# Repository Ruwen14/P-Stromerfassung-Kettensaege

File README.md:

# P-Stromerfassung-Kettensaege
Projektarbeit: Schaltungstechnik Master Mechatronik
- Aufgabenstellung:
  Messung des Dreiphasenstrom eines BLDC-Motors in einer Kettensäge

- Genutzte Technologien:
  -   LTSpice (Simulation)
  -   Eagle (Platinendesign & Layout)
  -   Reflow Ofen & Löteisen (Bestückung)

# Schematic

# PCB

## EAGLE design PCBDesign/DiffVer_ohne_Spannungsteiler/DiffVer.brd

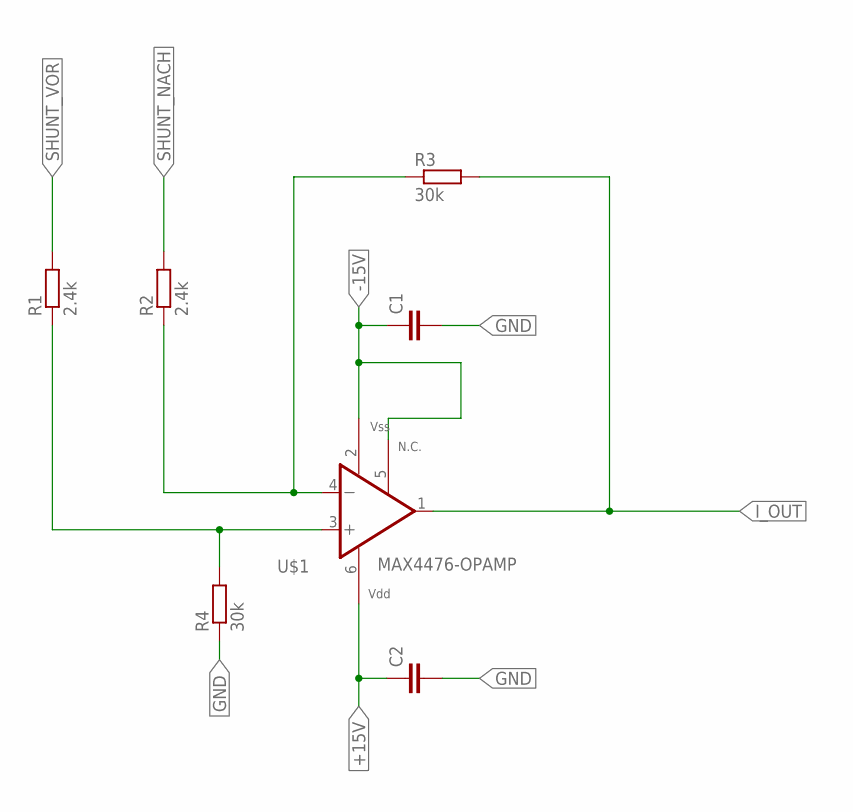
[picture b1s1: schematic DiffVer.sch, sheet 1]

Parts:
C1, C2: C-EUC0805; C0805
R1, R2: 2.4k; R0805
R3, R4: 30k; R0805
U$1: MAX4476-OPAMP; SOT23-6

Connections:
+15V: C2.1, U$1.6 (VDD); also elsewhere on the board
-15V: C1.1, U$1.2 (VSS), U$1.5 (NC); also elsewhere on the board
GND: C1.2, C2.2, R4.1; also elsewhere on the board
I_OUT: R3.2, U$1.1 (OUT); also elsewhere on the board
MINUS_OP: R2.1, R3.1, U$1.4 (-IN)
PLUS_OP: R1.1, R4.2, U$1.3 (+IN)
SHUNT_NACH: R2.2; also elsewhere on the board
SHUNT_VOR: R1.2; also elsewhere on the board

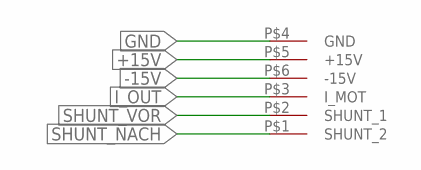
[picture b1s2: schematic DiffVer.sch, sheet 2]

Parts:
U$2: ADAPTERPLATINE_OPSHUNT

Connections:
+15V: U$2.P$5 (+15V); also elsewhere on the board
-15V: U$2.P$6 (-15V); also elsewhere on the board
GND: U$2.P$4 (GND); also elsewhere on the board
I_OUT: U$2.P$3 (I_MOT); also elsewhere on the board
SHUNT_NACH: U$2.P$1 (SHUNT_2); also elsewhere on the board
SHUNT_VOR: U$2.P$2 (SHUNT_1); also elsewhere on the board

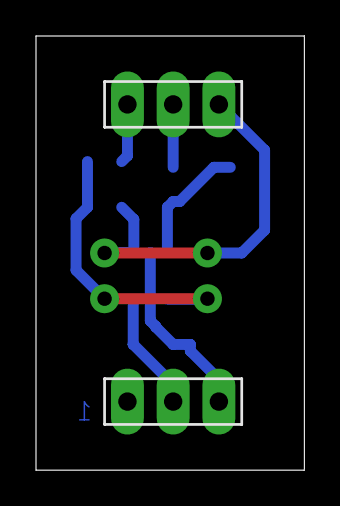
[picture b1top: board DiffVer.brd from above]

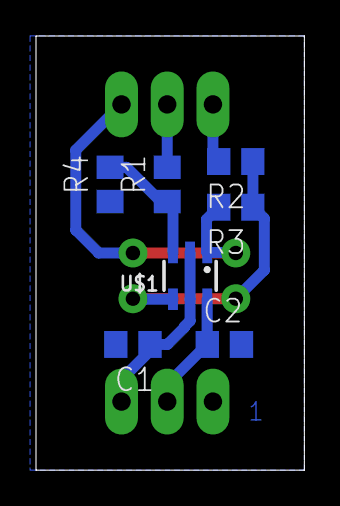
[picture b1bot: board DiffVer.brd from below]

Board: 2 copper layers, 14.9 x 24.1 mm, 8 parts (7 on the bottom side), 8 nets.

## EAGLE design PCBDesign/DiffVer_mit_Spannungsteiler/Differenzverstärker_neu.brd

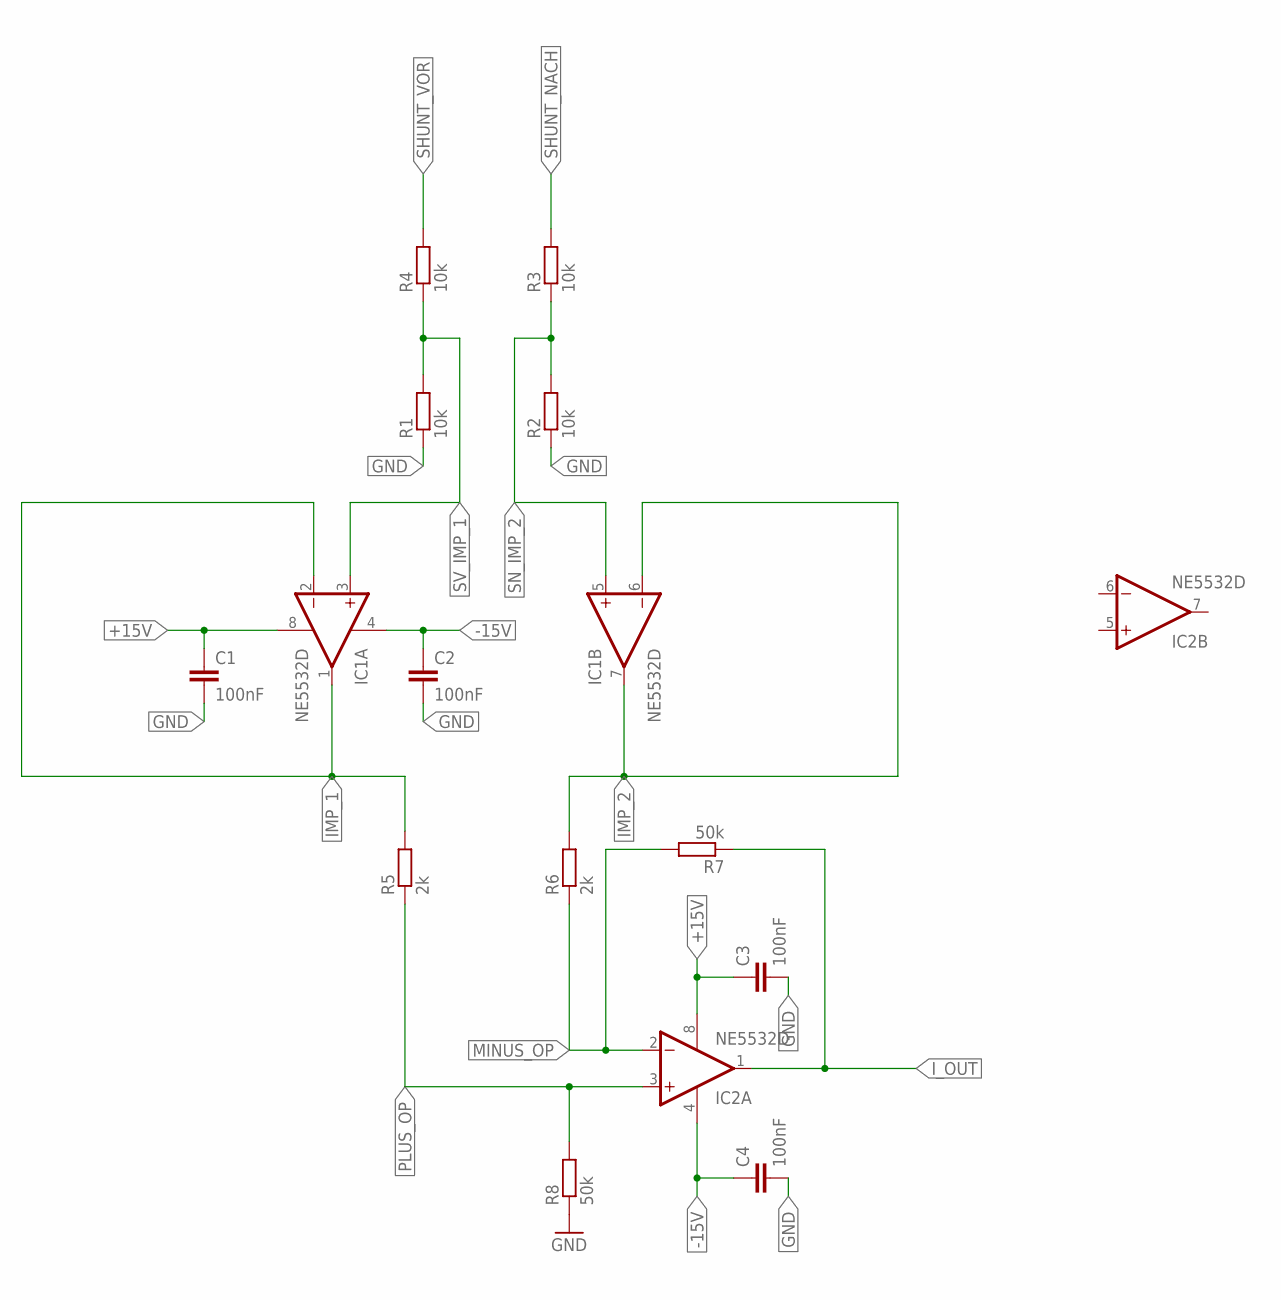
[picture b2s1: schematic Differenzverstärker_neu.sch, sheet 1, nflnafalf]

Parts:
C1, C2, C3, C4: 100nF; C0805
IC1, IC2: NE5532D; SO08
R1, R2, R3, R4: 10k; R0805
R5, R6: 2k; R0805
R7, R8: 50k; R0805

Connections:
+15V: C1.1, C3.1, IC1.8 (V+), IC2.8 (V+); also elsewhere on the board
-15V: C2.1, C4.1, IC1.4 (V-), IC2.4 (V-); also elsewhere on the board
GND: C1.2, C2.2, C3.2, C4.2, R1.1, R2.1, R8.1; also elsewhere on the board
IMP_1: IC1.1 (OUT), IC1.2 (-IN), R5.2
IMP_2: IC1.6 (-IN), IC1.7 (OUT), R6.2
I_OUT: IC2.1 (OUT), R7.1; also elsewhere on the board
MINUS_OP: IC2.2 (-IN), R6.1, R7.2
PLUS_OP: IC2.3 (+IN), R5.1, R8.2
SHUNT_NACH: R3.2; also elsewhere on the board
SHUNT_VOR: R4.2; also elsewhere on the board
SN_IMP_2: IC1.5 (+IN), R2.2, R3.1
SV_IMP_1: IC1.3 (+IN), R1.2, R4.1

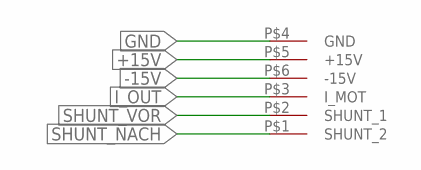
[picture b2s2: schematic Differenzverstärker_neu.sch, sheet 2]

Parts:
U$2: ADAPTERPLATINE_OPSHUNT

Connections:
+15V: U$2.P$5 (+15V); also elsewhere on the board
-15V: U$2.P$6 (-15V); also elsewhere on the board
GND: U$2.P$4 (GND); also elsewhere on the board
I_OUT: U$2.P$3 (I_MOT); also elsewhere on the board
SHUNT_NACH: U$2.P$1 (SHUNT_2); also elsewhere on the board
SHUNT_VOR: U$2.P$2 (SHUNT_1); also elsewhere on the board

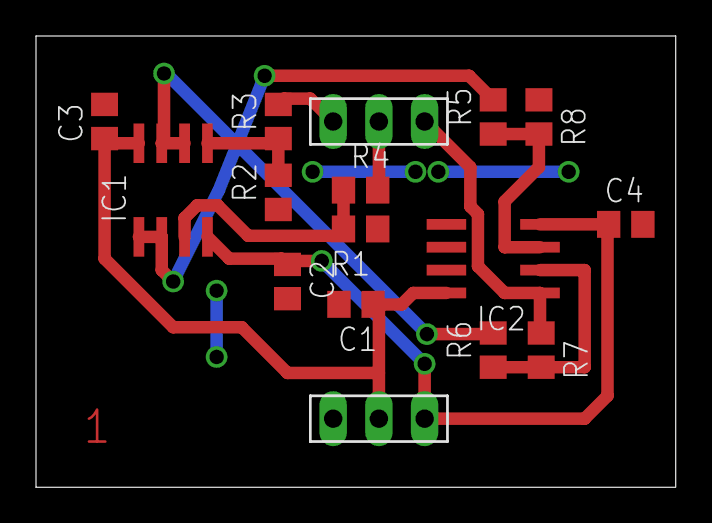
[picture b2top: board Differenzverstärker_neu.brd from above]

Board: 2 copper layers, 35.5 x 25.1 mm, 15 parts (0 on the bottom side), 12 nets.

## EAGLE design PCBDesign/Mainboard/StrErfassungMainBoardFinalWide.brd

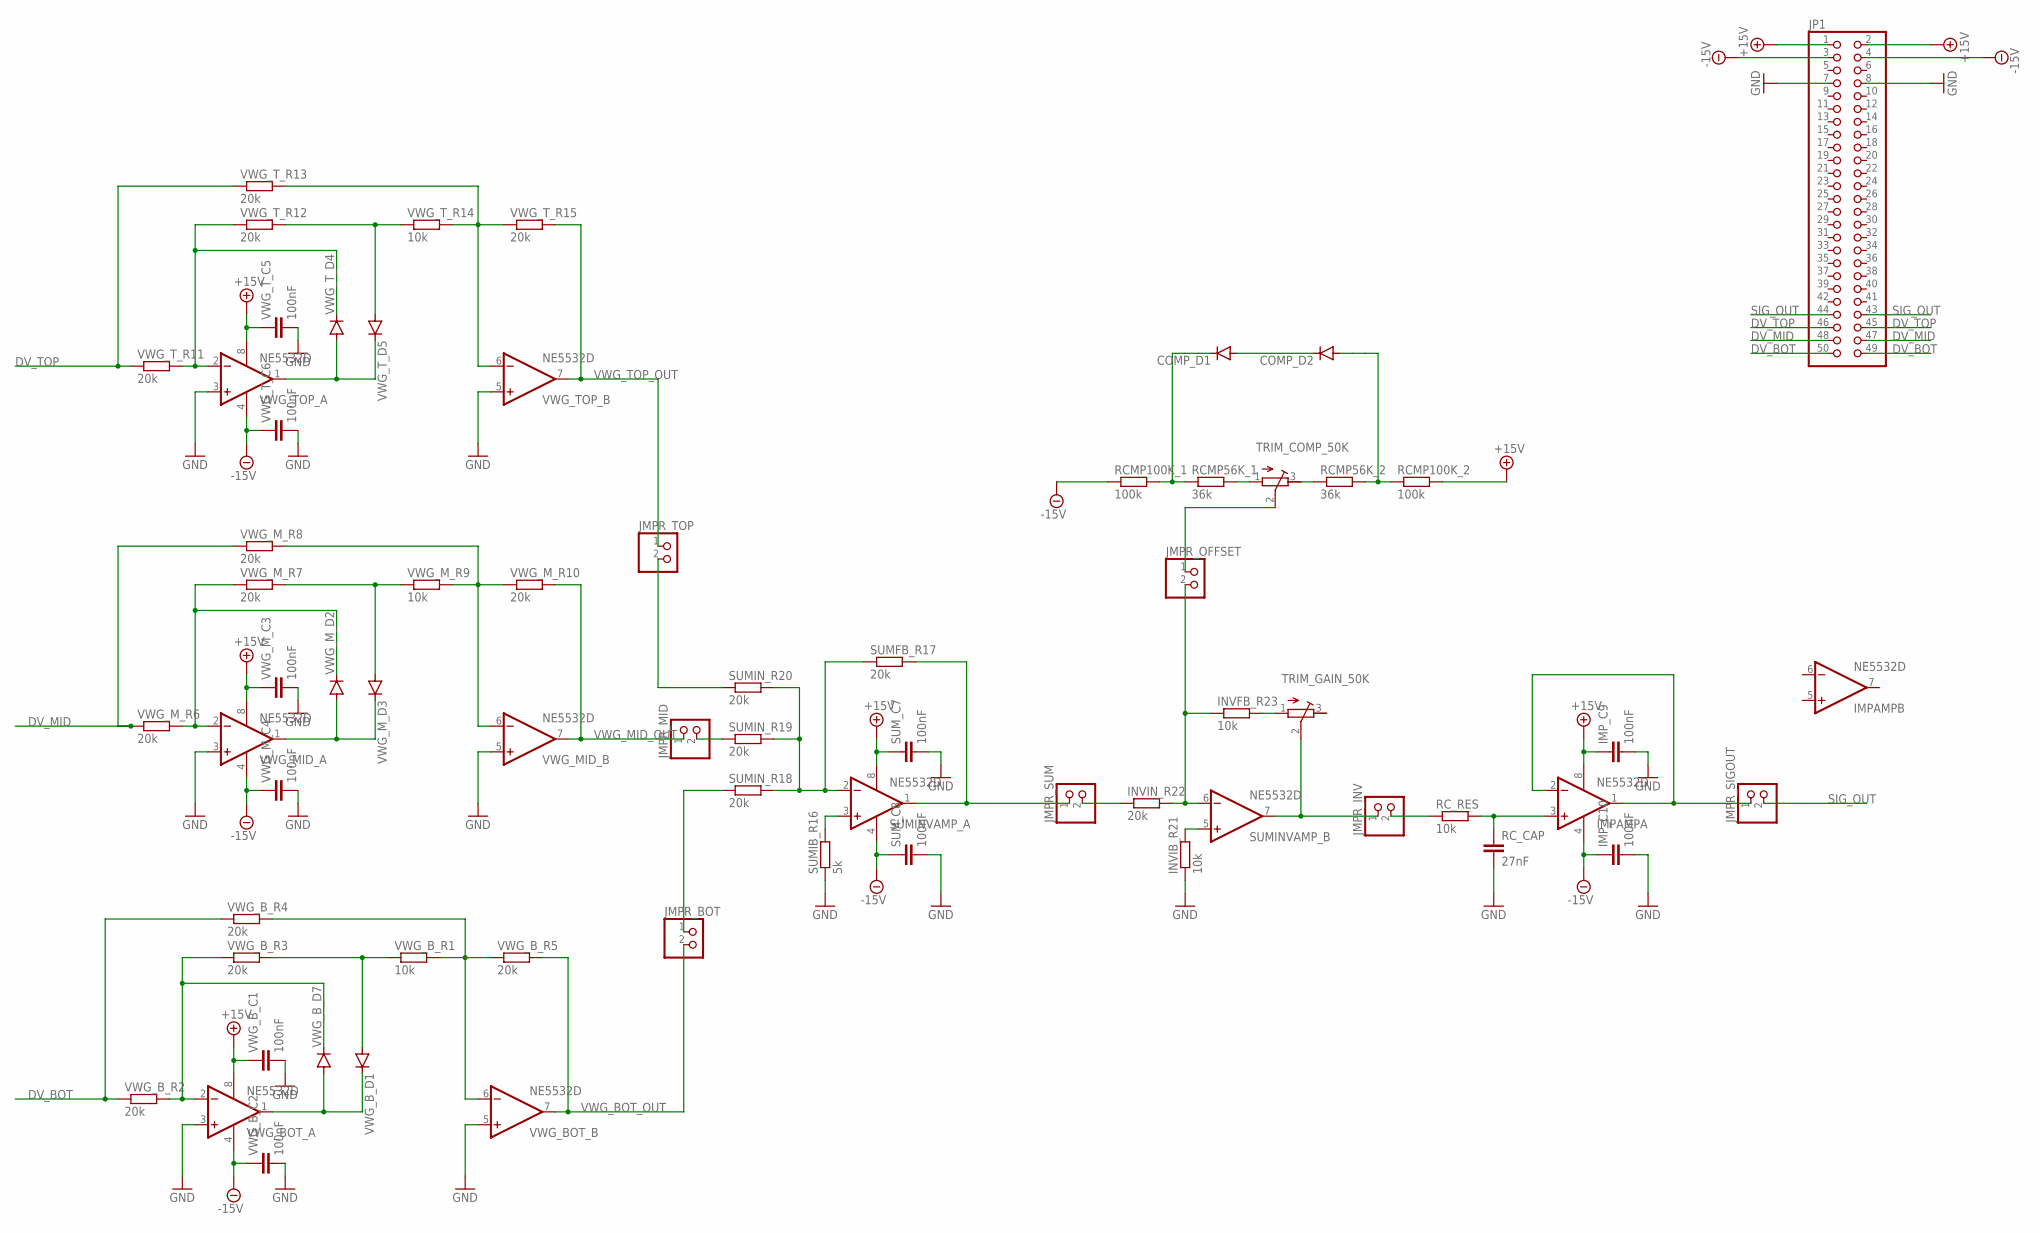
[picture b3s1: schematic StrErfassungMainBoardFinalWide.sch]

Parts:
COMP_D1, COMP_D2: DIODE-SOD123; SOD123
IMPAMP: NE5532D; SO08
IMP_C9, IMP_C10: 100nF; C0805
INVFB_R23: 10k; R0805
INVIB_R21: 10k; R0805
INVIN_R22: 20k; R0805
JMPR_BOT: PINHD-1X2; 1X02
JMPR_INV: PINHD-1X2; 1X02
JMPR_MID: PINHD-1X2; 1X02
JMPR_OFFSET: PINHD-1X2; 1X02
JMPR_SIGOUT: PINHD-1X2; 1X02
JMPR_SUM: PINHD-1X2; 1X02
JMPR_TOP: PINHD-1X2; 1X02
JP1: PINHD-2X25/90; 2X25/90
RCMP56K_1, RCMP56K_2: 36k; R0805
RCMP100K_1, RCMP100K_2: 100k; R0805
RC_CAP: 27nF; C0805
RC_RES: 10k; R0805
SUMFB_R17: 20k; R0805
SUMIB_R16: 5k; R0805
SUMINVAMP_: NE5532D; SO08
SUMIN_R18, SUMIN_R19, SUMIN_R20: 20k; R0805
SUM_C7, SUM_C8: 100nF; C0805
TRIM_COMP_50K: R-TRIMM3296W; RTRIM3296W
TRIM_GAIN_50K: R-TRIMM3296W; RTRIM3296W
VWG_BOT_: NE5532D; SO08
VWG_B_C1, VWG_B_C2: 100nF; C0805
VWG_B_D1, VWG_B_D7: DIODE-SOD123; SOD123
VWG_B_R1: 10k; R0805
VWG_B_R2, VWG_B_R3, VWG_B_R4, VWG_B_R5: 20k; R0805
VWG_MID_: NE5532D; SO08
VWG_M_C3, VWG_M_C4: 100nF; C0805
VWG_M_D2, VWG_M_D3: DIODE-SOD123; SOD123
VWG_M_R6, VWG_M_R7, VWG_M_R8, VWG_M_R10: 20k; R0805
VWG_M_R9: 10k; R0805
VWG_TOP_: NE5532D; SO08
VWG_T_C5, VWG_T_C6: 100nF; C0805
VWG_T_D4, VWG_T_D5: DIODE-SOD123; SOD123
VWG_T_R11, VWG_T_R12, VWG_T_R13, VWG_T_R15: 20k; R0805
VWG_T_R14: 10k; R0805

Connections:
+15V: IMPAMP.8 (V+), IMP_C9.1, JP1.1, JP1.2, RCMP100K_2.2, SUMINVAMP_.8 (V+), SUM_C7.1, VWG_BOT_.8 (V+), VWG_B_C1.1, VWG_MID_.8 (V+), VWG_M_C3.1, VWG_TOP_.8 (V+), VWG_T_C5.1
-15V: IMPAMP.4 (V-), IMP_C10.1, JP1.3, JP1.4, RCMP100K_1.1, SUMINVAMP_.4 (V-), SUM_C8.1, VWG_BOT_.4 (V-), VWG_B_C2.1, VWG_MID_.4 (V-), VWG_M_C4.1, VWG_TOP_.4 (V-), VWG_T_C6.1
DV_BOT: JP1.49 (50), JP1.50 (49), VWG_B_R2.1, VWG_B_R4.1
DV_MID: JP1.47 (48), JP1.48 (47), VWG_M_R6.1, VWG_M_R8.1
DV_TOP: JP1.45 (46), JP1.46 (45), VWG_T_R11.1, VWG_T_R13.1
GND: IMP_C9.2, IMP_C10.2, INVIB_R21.1, JP1.7, JP1.8, RC_CAP.2, SUMIB_R16.1, SUM_C7.2, SUM_C8.2, VWG_BOT_.3 (+IN), VWG_BOT_.5 (+IN), VWG_B_C1.2, VWG_B_C2.2, VWG_MID_.3 (+IN), VWG_MID_.5 (+IN), VWG_M_C3.2, VWG_M_C4.2, VWG_TOP_.3 (+IN), VWG_TOP_.5 (+IN), VWG_T_C5.2, VWG_T_C6.2
JMPR_INV: JMPR_INV.1, SUMINVAMP_.7 (OUT), TRIM_GAIN_50K.2 (S)
unnamed: VWG_B_D1.A, VWG_B_R1.1, VWG_B_R3.2
unnamed: VWG_BOT_.1 (OUT), VWG_B_D1.C, VWG_B_D7.A
unnamed: VWG_MID_.2 (-IN), VWG_M_D2.C, VWG_M_R6.2, VWG_M_R7.1
unnamed: VWG_M_D3.A, VWG_M_R7.2, VWG_M_R9.1
unnamed: VWG_BOT_.6 (-IN), VWG_B_R1.2, VWG_B_R4.2, VWG_B_R5.1
unnamed: VWG_MID_.1 (OUT), VWG_M_D2.A, VWG_M_D3.C
unnamed: SUMFB_R17.1, SUMINVAMP_.2 (-IN), SUMIN_R18.2, SUMIN_R19.2, SUMIN_R20.2
unnamed: VWG_MID_.6 (-IN), VWG_M_R8.2, VWG_M_R9.2, VWG_M_R10.1
unnamed: INVIB_R21.2, SUMINVAMP_.5 (+IN)
unnamed: VWG_TOP_.2 (-IN), VWG_T_D4.C, VWG_T_R11.2, VWG_T_R12.1
unnamed: VWG_T_D5.A, VWG_T_R12.2, VWG_T_R14.1
unnamed: VWG_TOP_.1 (OUT), VWG_T_D4.A, VWG_T_D5.C
unnamed: VWG_TOP_.6 (-IN), VWG_T_R13.2, VWG_T_R14.2, VWG_T_R15.1
unnamed: INVFB_R23.1, INVIN_R22.2, JMPR_OFFSET.2, SUMINVAMP_.6 (-IN)
unnamed: SUMIB_R16.2, SUMINVAMP_.3 (+IN)
unnamed: JMPR_OFFSET.1, TRIM_COMP_50K.2 (S)
unnamed: JMPR_SUM.1, SUMFB_R17.2, SUMINVAMP_.1 (OUT)
unnamed: IMPAMP.3 (+IN), RC_CAP.1, RC_RES.2
unnamed: RCMP56K_2.1, TRIM_COMP_50K.3 (E)
unnamed: COMP_D2.A, RCMP56K_2.2, RCMP100K_2.1
unnamed: COMP_D1.C, RCMP56K_1.1, RCMP100K_1.2
unnamed: RCMP56K_1.2, TRIM_COMP_50K.1 (A)
unnamed: COMP_D1.A, COMP_D2.C
unnamed: INVFB_R23.2, TRIM_GAIN_50K.1 (A)
unnamed: INVIN_R22.1, JMPR_SUM.2
unnamed: JMPR_BOT.1, SUMIN_R18.1
unnamed: JMPR_TOP.2, SUMIN_R20.1
unnamed: JMPR_MID.2, SUMIN_R19.1
unnamed: JMPR_INV.2, RC_RES.1
SIG_OUT: IMPAMP.1 (OUT), IMPAMP.2 (-IN), JMPR_SIGOUT.1, JMPR_SIGOUT.2, JP1.43 (44), JP1.44 (43)
VWG_BOT_OUT: JMPR_BOT.2, VWG_BOT_.7 (OUT), VWG_B_R5.2
VWG_IN-: VWG_BOT_.2 (-IN), VWG_B_D7.C, VWG_B_R2.2, VWG_B_R3.1
VWG_MID_OUT: JMPR_MID.1, VWG_MID_.7 (OUT), VWG_M_R10.2
VWG_TOP_OUT: JMPR_TOP.1, VWG_TOP_.7 (OUT), VWG_T_R15.2

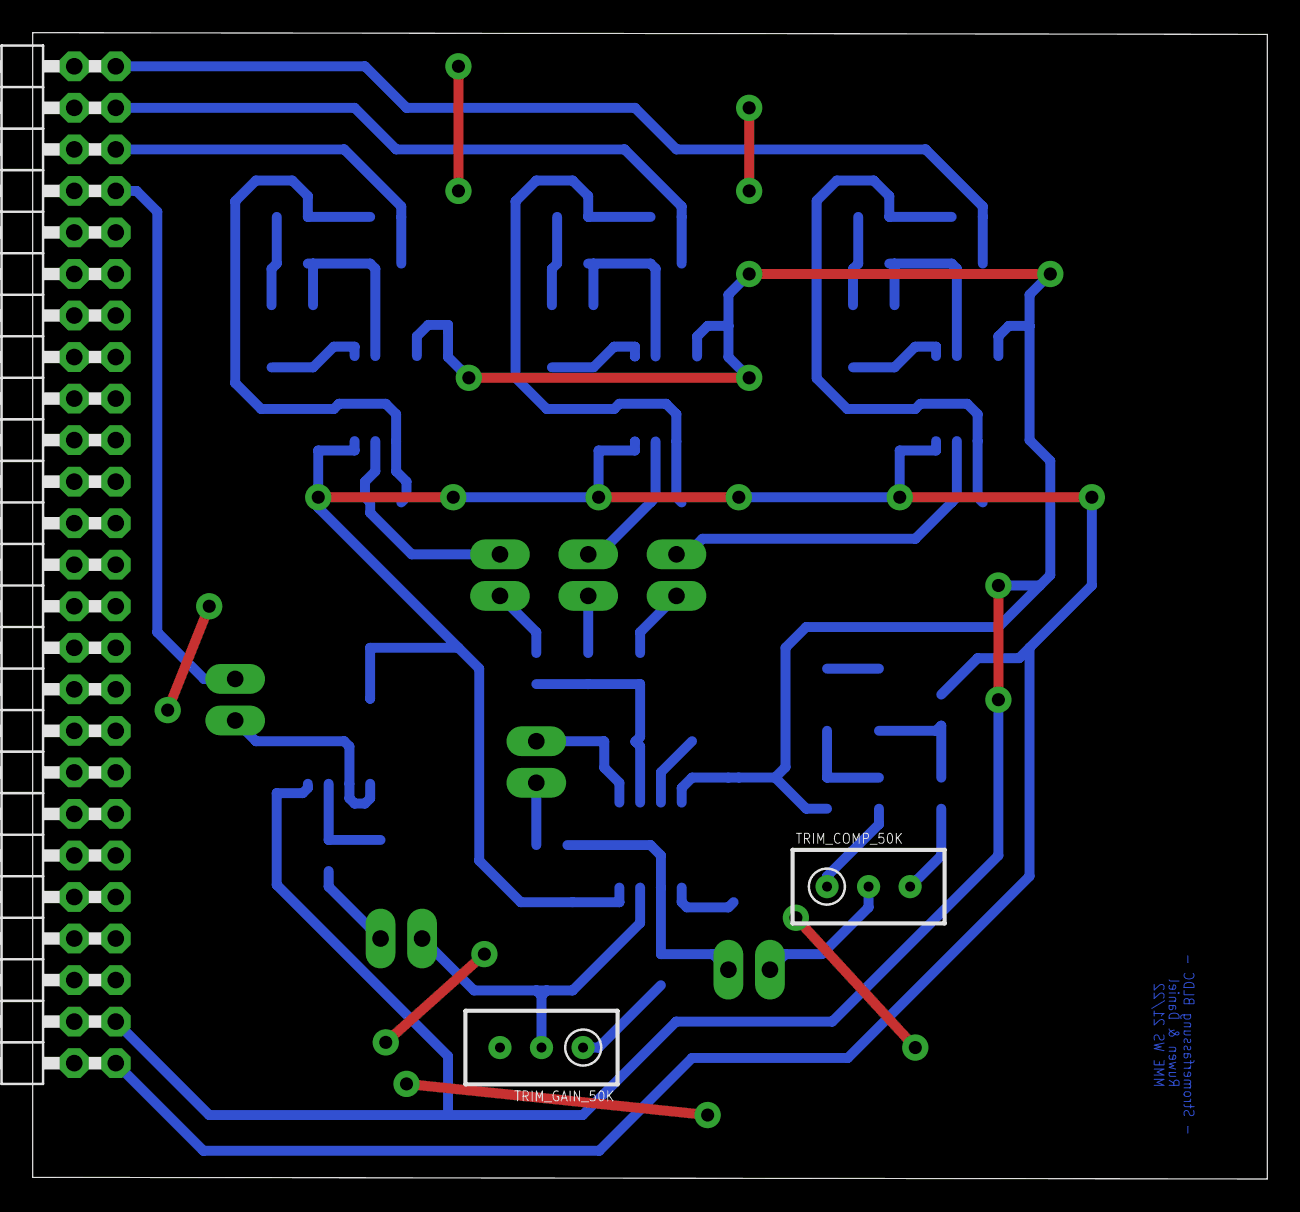
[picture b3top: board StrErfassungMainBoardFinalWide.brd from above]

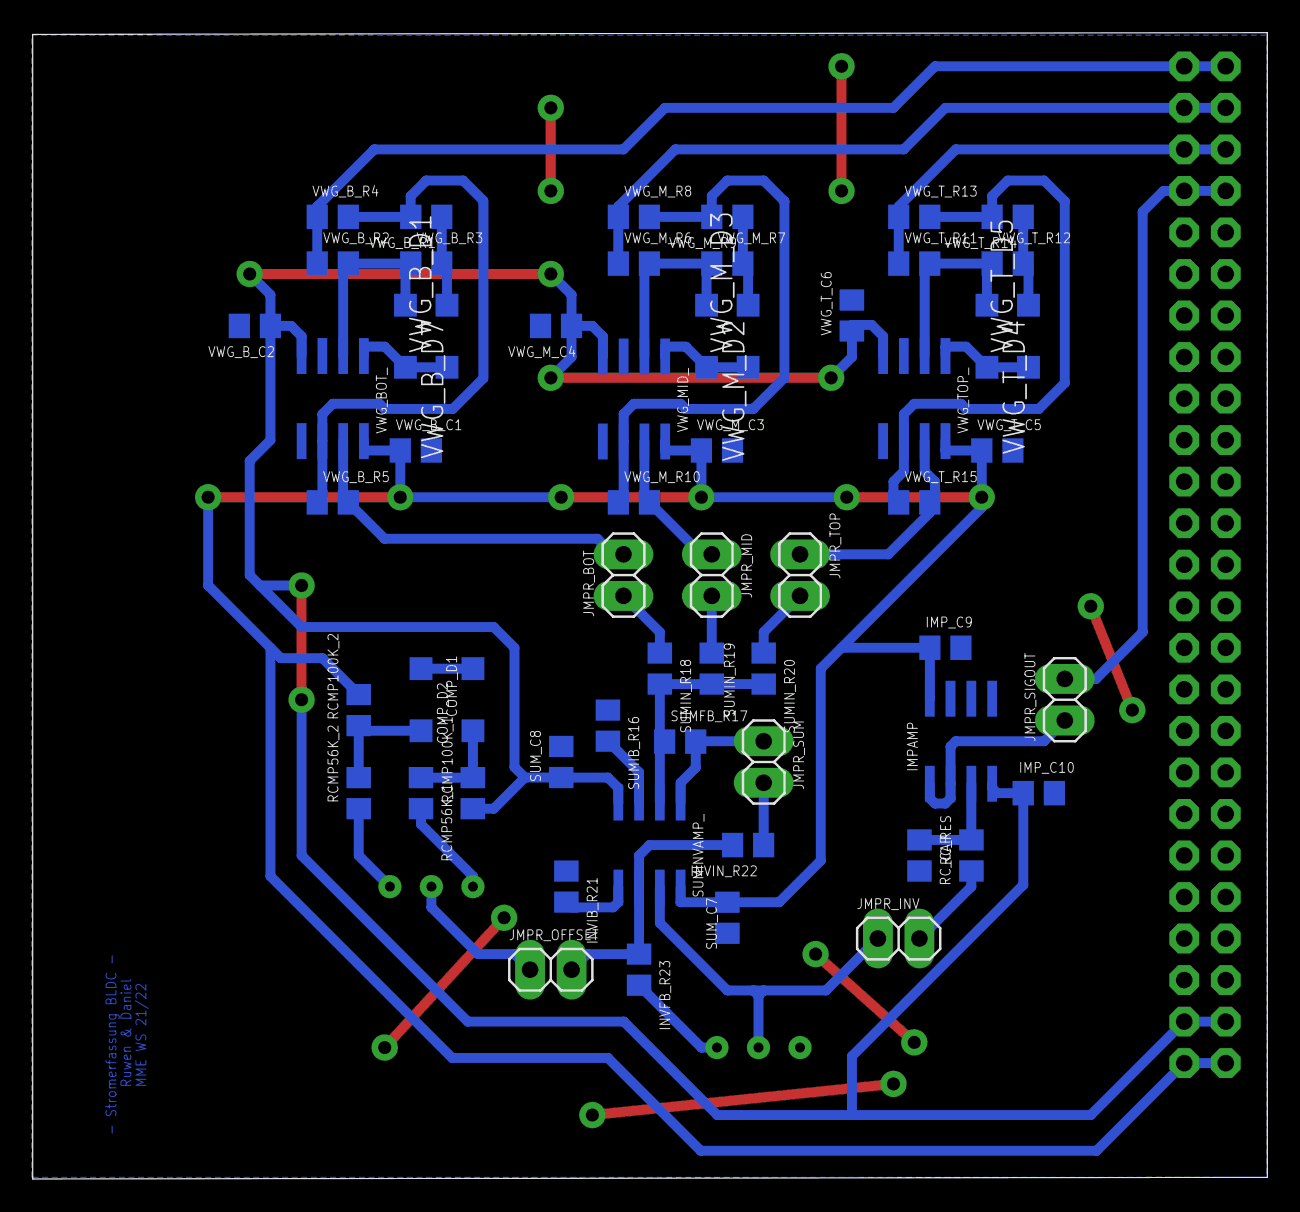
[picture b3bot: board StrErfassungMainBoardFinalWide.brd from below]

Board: 2 copper layers, 75.5 x 70.1 mm, 62 parts (59 on the bottom side), 41 nets.

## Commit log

2022-04-22 Add PCB-Design Files
2022-04-22 Add LTSpice-Simulations
2022-04-22 add final presentation
2022-04-22 added schematic
2022-04-22 added pcb view
2022-04-22 add License
